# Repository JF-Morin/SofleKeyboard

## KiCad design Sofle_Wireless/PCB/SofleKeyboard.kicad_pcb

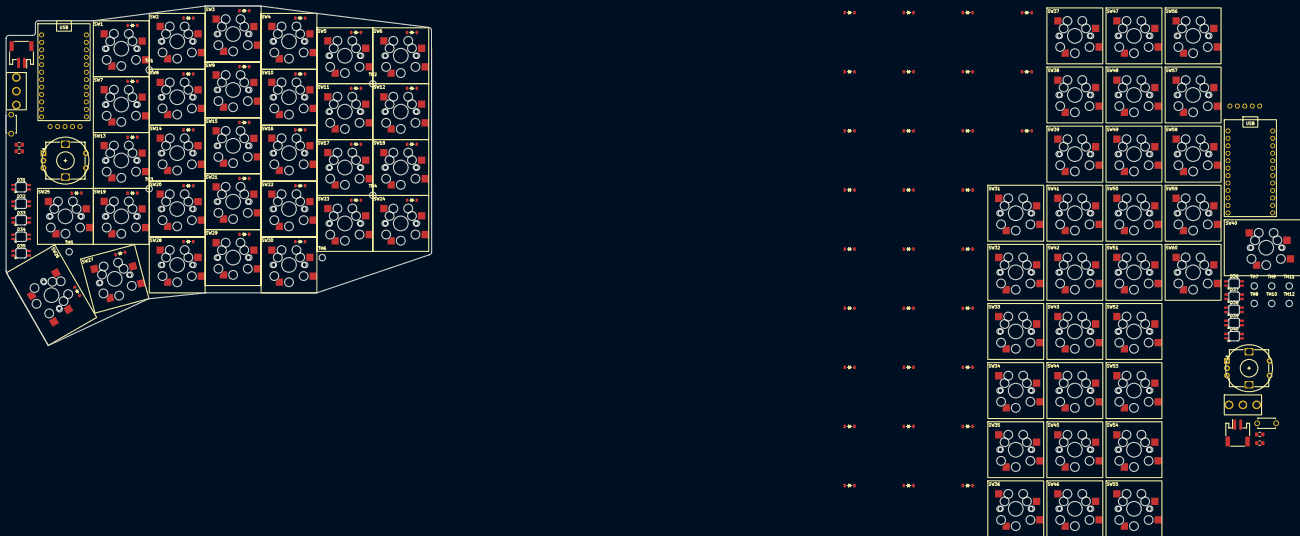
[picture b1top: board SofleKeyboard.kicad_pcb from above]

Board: 2 copper layers, 420.3 x 115.7 mm, 158 parts (0 on the bottom side), 91 nets, no tracks yet.

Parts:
D1, D2, D3, D4, D5, D6, D7, D8, D9, D10, D11, D12, D13, D14, D15, D16, D17, D18, D19, D20, D21, D22, D23, D24, D25, D26, D27, D28, D29, D30, D41, D42, D43, D44, D45, D46, D47, D48, D49, D50, D51, D52, D53, D54, D55, D56, D57, D58, D59, D60, D61, D62, D63, D64, D65, D66, D67, D68, D69, D70: D; Diode_SOD-123(dual side)
D31, D32, D33, D34, D35, D36, D37, D38, D39, D40: LED_SK6812MINI; SK6812_Mini-E_DualSide
EC1, EC2: Rotary_Encoder_Switch; RotaryEncoder_Alps_EC12E-Switch_Vertical_H20mm
J1, J3: Conn_01x05; NICE!VIEW
J2, J4: Conn_01x02; JST_PH_S2B-PH-SM4-TB_1x02-1MP_P2.00mm_Horizontal_DualSide
PWR_SW1, PWR_SW2: Switch; SLW-1276864-4A-D
R1, R2, R3, R4: R; R_0805_2012Metric_Pad1.20x1.40mm_HandSolder_dualside
RSW1, RSW2: SW_RST; ResetSW_DualSide
SW1, SW31: SW1; SW_MXHS_CHOCV1V2HS_1U
SW2, SW36: SW2; SW_MXHS_CHOCV1V2HS_1U
SW3, SW41: SW3; SW_MXHS_CHOCV1V2HS_1U
SW4, SW46: SW4; SW_MXHS_CHOCV1V2HS_1U
SW5, SW51: SW5; SW_MXHS_CHOCV1V2HS_1U
SW6, SW56: SW6; SW_MXHS_CHOCV1V2HS_1U
SW7, SW32: SW7; SW_MXHS_CHOCV1V2HS_1U
SW8, SW37: SW8; SW_MXHS_CHOCV1V2HS_1U
SW9, SW42: SW9; SW_MXHS_CHOCV1V2HS_1U
SW10, SW47: SW10; SW_MXHS_CHOCV1V2HS_1U
SW11, SW52: SW11; SW_MXHS_CHOCV1V2HS_1U
SW12, SW57: SW12; SW_MXHS_CHOCV1V2HS_1U
SW13, SW33: SW13; SW_MXHS_CHOCV1V2HS_1U
SW14, SW38: SW14; SW_MXHS_CHOCV1V2HS_1U
SW15, SW43: SW15; SW_MXHS_CHOCV1V2HS_1U
SW16, SW48: SW16; SW_MXHS_CHOCV1V2HS_1U
SW17, SW53: SW17; SW_MXHS_CHOCV1V2HS_1U
SW18, SW58: SW18; SW_MXHS_CHOCV1V2HS_1U
SW19, SW25, SW34, SW35: SW19; SW_MXHS_CHOCV1V2HS_1U
SW20, SW39: SW20; SW_MXHS_CHOCV1V2HS_1U
SW21, SW44: SW21; SW_MXHS_CHOCV1V2HS_1U
SW22, SW49: SW22; SW_MXHS_CHOCV1V2HS_1U
SW23, SW54: SW23; SW_MXHS_CHOCV1V2HS_1U
SW24, SW59: SW24; SW_MXHS_CHOCV1V2HS_1U
SW26, SW40: SW26; SW_MXHS_CHOCV1V2HS_1.5U
SW27, SW45: SW27; SW_MXHS_CHOCV1V2HS_1U
SW28, SW50: SW28; SW_MXHS_CHOCV1V2HS_1U
SW29, SW55: SW29; SW_MXHS_CHOCV1V2HS_1U
SW30, SW60: SW30; SW_MXHS_CHOCV1V2HS_1U
TH1, TH2, TH3, TH4, TH5, TH6, TH7, TH8, TH9, TH10, TH11, TH12: HOLE; MountingHole_2.2mm_M2
U1, U2: NICE!NANO

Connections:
BATT+: PWR_SW1.2, PWR_SW2.2, U1.1 (EXT1), U2.1 (EXT1)
CS: J1.5, J3.5, U1.24 (INT1), U2.24 (INT1)
ENCA: EC1.A, EC2.A, U1.5 (EXT5), U2.5 (EXT5)
ENCB: EC1.B, EC2.B, U1.6 (EXT6), U2.6 (EXT6)
GND: D31.3 (GND), D32.3 (GND), D33.3 (GND), D34.3 (GND), D35.3 (GND), D36.3 (GND), D37.3 (GND), D38.3 (GND), D39.3 (GND), D40.3 (GND), EC1.C, EC2.C, J1.4, J2.2, J3.4, J4.2, RSW1.1, RSW2.1, U1.2 (EXT2), U1.21 (INT4), U1.22 (INT3), U2.2 (EXT2), U2.21 (INT4), U2.22 (INT3)
LED: D31.4 (DIN), D36.4 (DIN), U1.23 (INT2), U2.23 (INT2)
unnamed: D1.2 (A), SW1.2
unnamed: D2.2 (A), SW2.2
unnamed: D3.2 (A), SW3.2
unnamed: D4.2 (A), SW4.2
unnamed: D5.2 (A), SW5.2
unnamed: D6.2 (A), SW6.2
unnamed: D7.2 (A), SW7.2
unnamed: D8.2 (A), SW8.2
unnamed: D9.2 (A), SW9.2
unnamed: D10.2 (A), SW10.2
unnamed: D11.2 (A), SW11.2
unnamed: D12.2 (A), SW12.2
unnamed: D13.2 (A), SW13.2
unnamed: D14.2 (A), SW14.2
unnamed: D15.2 (A), SW15.2
unnamed: D16.2 (A), SW16.2
unnamed: D17.2 (A), SW17.2
unnamed: D18.2 (A), SW18.2
unnamed: D19.2 (A), SW19.2
unnamed: D20.2 (A), SW20.2
unnamed: D21.2 (A), SW21.2
unnamed: D22.2 (A), SW22.2
unnamed: D23.2 (A), SW23.2
unnamed: D24.2 (A), SW24.2
unnamed: D25.2 (A), EC1.S2, SW25.2
unnamed: D26.2 (A), SW26.2
unnamed: D27.2 (A), SW27.2
unnamed: D28.2 (A), SW28.2
unnamed: D29.2 (A), SW29.2
unnamed: D30.2 (A), SW30.2
unnamed: D31.2 (DOUT), D32.4 (DIN)
unnamed: D32.2 (DOUT), D33.4 (DIN)
unnamed: D33.2 (DOUT), D34.4 (DIN)
unnamed: D34.2 (DOUT), D35.4 (DIN)
unnamed: D36.2 (DOUT), D37.4 (DIN)
unnamed: D37.2 (DOUT), D38.4 (DIN)
unnamed: D38.2 (DOUT), D39.4 (DIN)
unnamed: D39.2 (DOUT), D40.4 (DIN)
unnamed: D41.2 (A), SW31.2
unnamed: D42.2 (A), SW32.2
unnamed: D43.2 (A), SW33.2
unnamed: D44.2 (A), SW34.2
unnamed: D45.2 (A), EC2.S2, SW35.2
unnamed: D46.2 (A), SW36.2
unnamed: D47.2 (A), SW37.2
unnamed: D48.2 (A), SW38.2
unnamed: D49.2 (A), SW39.2
unnamed: D50.2 (A), SW40.2
unnamed: D51.2 (A), SW41.2
unnamed: D52.2 (A), SW42.2
unnamed: D53.2 (A), SW43.2
unnamed: D54.2 (A), SW44.2
unnamed: D55.2 (A), SW45.2
unnamed: D56.2 (A), SW46.2
unnamed: D57.2 (A), SW47.2
unnamed: D58.2 (A), SW48.2
unnamed: D59.2 (A), SW49.2
unnamed: D60.2 (A), SW50.2
unnamed: D61.2 (A), SW51.2
unnamed: D62.2 (A), SW52.2
unnamed: D63.2 (A), SW53.2
unnamed: D64.2 (A), SW54.2
unnamed: D65.2 (A), SW55.2
unnamed: D66.2 (A), SW56.2
unnamed: D67.2 (A), SW57.2
unnamed: D68.2 (A), SW58.2
unnamed: D69.2 (A), SW59.2
unnamed: D70.2 (A), SW60.2
unnamed: J2.1, PWR_SW1.1
unnamed: J4.1, PWR_SW2.1
RESET: RSW1.2, RSW2.2, U1.3 (EXT3), U2.3 (EXT3)
SCL: J1.2, J3.2, R2.2, R4.2, U1.19 (INT6), U2.19 (INT6)
SDA: J1.1, J3.1, R1.2, R3.2, U1.20 (INT5), U2.20 (INT5)
VCC: D31.1 (VDD), D32.1 (VDD), D33.1 (VDD), D34.1 (VDD), D35.1 (VDD), D36.1 (VDD), D37.1 (VDD), D38.1 (VDD), D39.1 (VDD), D40.1 (VDD), J1.3, J3.3, R1.1, R2.1, R3.1, R4.1, U1.4 (EXT4), U2.4 (EXT4)
col0: SW6.1, SW12.1, SW18.1, SW24.1, SW30.1, SW56.1, SW57.1, SW58.1, SW59.1, SW60.1, U1.7 (EXT7), U2.7 (EXT7)
col1: SW5.1, SW11.1, SW17.1, SW23.1, SW29.1, SW51.1, SW52.1, SW53.1, SW54.1, SW55.1, U1.8 (EXT8), U2.8 (EXT8)
col2: SW4.1, SW10.1, SW16.1, SW22.1, SW28.1, SW46.1, SW47.1, SW48.1, SW49.1, SW50.1, U1.9 (EXT9), U2.9 (EXT9)
col3: SW3.1, SW9.1, SW15.1, SW21.1, SW27.1, SW41.1, SW42.1, SW43.1, SW44.1, SW45.1, U1.10 (EXT10), U2.10 (EXT10)
col4: SW2.1, SW8.1, SW14.1, SW20.1, SW26.1, SW36.1, SW37.1, SW38.1, SW39.1, SW40.1, U1.11 (EXT11), U2.11 (EXT11)
col5: EC1.S1, EC2.S1, SW1.1, SW7.1, SW13.1, SW19.1, SW25.1, SW31.1, SW32.1, SW33.1, SW34.1, SW35.1, U1.12 (EXT12), U2.12 (EXT12)
row0: D1.1 (K), D2.1 (K), D3.1 (K), D4.1 (K), D5.1 (K), D6.1 (K), D41.1 (K), D46.1 (K), D51.1 (K), D56.1 (K), D61.1 (K), D66.1 (K), U1.17 (INT8), U2.17 (INT8)
row1: D7.1 (K), D8.1 (K), D9.1 (K), D10.1 (K), D11.1 (K), D12.1 (K), D42.1 (K), D47.1 (K), D52.1 (K), D57.1 (K), D62.1 (K), D67.1 (K), U1.16 (INT9), U2.16 (INT9)
row2: D13.1 (K), D14.1 (K), D15.1 (K), D16.1 (K), D17.1 (K), D18.1 (K), D43.1 (K), D48.1 (K), D53.1 (K), D58.1 (K), D63.1 (K), D68.1 (K), U1.15 (INT10), U2.15 (INT10)
row3: D19.1 (K), D20.1 (K), D21.1 (K), D22.1 (K), D23.1 (K), D24.1 (K), D44.1 (K), D49.1 (K), D54.1 (K), D59.1 (K), D64.1 (K), D69.1 (K), U1.14 (INT11), U2.14 (INT11)
row4: D25.1 (K), D26.1 (K), D27.1 (K), D28.1 (K), D29.1 (K), D30.1 (K), D45.1 (K), D50.1 (K), D55.1 (K), D60.1 (K), D65.1 (K), D70.1 (K), U1.13 (INT12), U2.13 (INT12)

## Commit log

2024-01-27 Work on Sofle Wireless Added footprints Placement of footprints
2024-02-11 Work on Footprints, PCB and schematic
2024-02-16 Work on traces
2024-02-19 Work on part placement and trace routing.
2024-02-24 Added BOM
2024-02-27 Project STALL Added filled area for GND: cannot connect all grounds with 2 layer board
    Wiser solution: make one board per side
2024-02-29 Exploration of multiple sheet for Schematic
